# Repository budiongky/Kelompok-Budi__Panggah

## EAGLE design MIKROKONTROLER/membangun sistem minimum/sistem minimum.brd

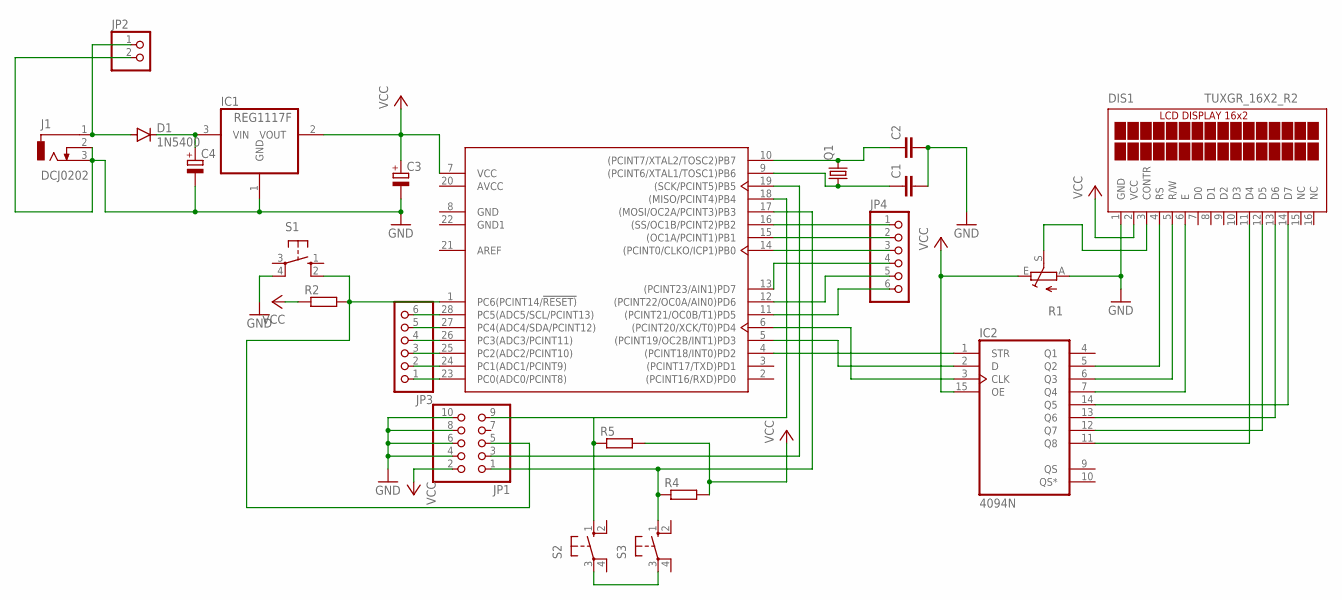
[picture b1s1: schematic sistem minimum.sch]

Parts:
C1, C2: C2,5-3; C2.5-3
C3, C4: CPOL-EUE2.5-6; E2,5-6
D1: 1N5400; DO201-15
DIS1: TUXGR_16X2_R2
IC1: REG1117F; DD-3
IC2: 4094N; DIL16
J1: DCJ0202
JP1: PINHD-2X5; 2X05
JP2: PINHD-1X2; 1X02
JP3, JP4: PINHD-1X6; 1X06
Q1: CRYSTALHC49S; HC49/S
R1: TRIM_EU-B25P; B25P
R2, R4, R5: R-EU_0204/7; 0204/7
S1, S2, S3: 10-XX; B3F-10XX
U1: ATMEGA328P-PU; DIP-28

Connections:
AVCC: U1.20 (AVCC)
GND: C1.2, C2.2, C3.-, C4.-, DIS1.1 (GND), IC1.1 (GND), J1.2, J1.3, JP1.4, JP1.6, JP1.8, JP1.10, JP2.2, R1.A, S1.4 (P1), U1.8 (GND)
GND1: U1.22 (GND1)
unnamed: C2.1, Q1.2, U1.10 ((PCINT7/XTAL2/TOSC2)PB7)
unnamed: C1.1, Q1.1, U1.9 ((PCINT6/XTAL1/TOSC1)PB6)
unnamed: JP1.9, U1.18 ((MISO/PCINT4)PB4)
unnamed: JP1.5, R2.2, S1.2 (S1), U1.1 (PC6(PCINT14/!RESET))
unnamed: JP1.3, U1.19 ((SCK/PCINT5)PB5)
unnamed: JP1.1, R4.1, S3.1 (S), U1.17 ((MOSI/OC2A/PCINT3)PB3)
unnamed: S2.3, S3.3
unnamed: C4.+, D1.C, IC1.3 (VIN)
unnamed: D1.A, J1.1, JP2.1
unnamed: R5.1, S2.1 (S)
unnamed: IC2.1 (STR), U1.4 ((PCINT18/INT0)PD2)
unnamed: IC2.2 (D), U1.5 ((PCINT19/OC2B/INT1)PD3)
unnamed: IC2.3 (CLK), U1.6 ((PCINT20/XCK/T0)PD4)
unnamed: DIS1.4 (RS), IC2.5 (Q2)
unnamed: DIS1.5 (R/W), IC2.6 (Q3)
unnamed: DIS1.6 (E), IC2.7 (Q4)
unnamed: DIS1.11 (D4), IC2.11 (Q8)
unnamed: DIS1.12 (D5), IC2.12 (Q7)
unnamed: DIS1.13 (D6), IC2.13 (Q6)
unnamed: DIS1.14 (D7), IC2.14 (Q5)
unnamed: JP3.6, U1.28 (PC5(ADC5/SCL/PCINT13))
unnamed: DIS1.3 (CONTR), R1.S
unnamed: JP3.5, U1.27 (PC4(ADC4/SDA/PCINT12))
unnamed: JP3.4, U1.26 (PC3(ADC3/PCINT11))
unnamed: JP3.3, U1.25 (PC2(ADC2/PCINT10))
unnamed: JP3.2, U1.24 (PC1(ADC1/PCINT9))
unnamed: JP3.1, U1.23 (PC0(ADC0/PCINT8))
unnamed: JP4.1, U1.16 ((SS/OC1B/PCINT2)PB2)
unnamed: JP4.2, U1.15 ((OC1A/PCINT1)PB1)
unnamed: JP4.3, U1.14 ((PCINT0/CLKO/ICP1)PB0)
unnamed: JP4.4, U1.13 ((PCINT23/AIN1)PD7)
unnamed: JP4.5, U1.12 ((PCINT22/OC0A/AIN0)PD6)
unnamed: JP4.6, U1.11 ((PCINT21/OC0B/T1)PD5)
VCC: C3.+, DIS1.2 (VCC), IC1.2 (VOUT), IC2.15 (OE), JP1.2, R1.E, R2.1, R4.2, R5.2, U1.7 (VCC)
VDD: IC2.16 (VDD)
VSS: IC2.8 (VSS)

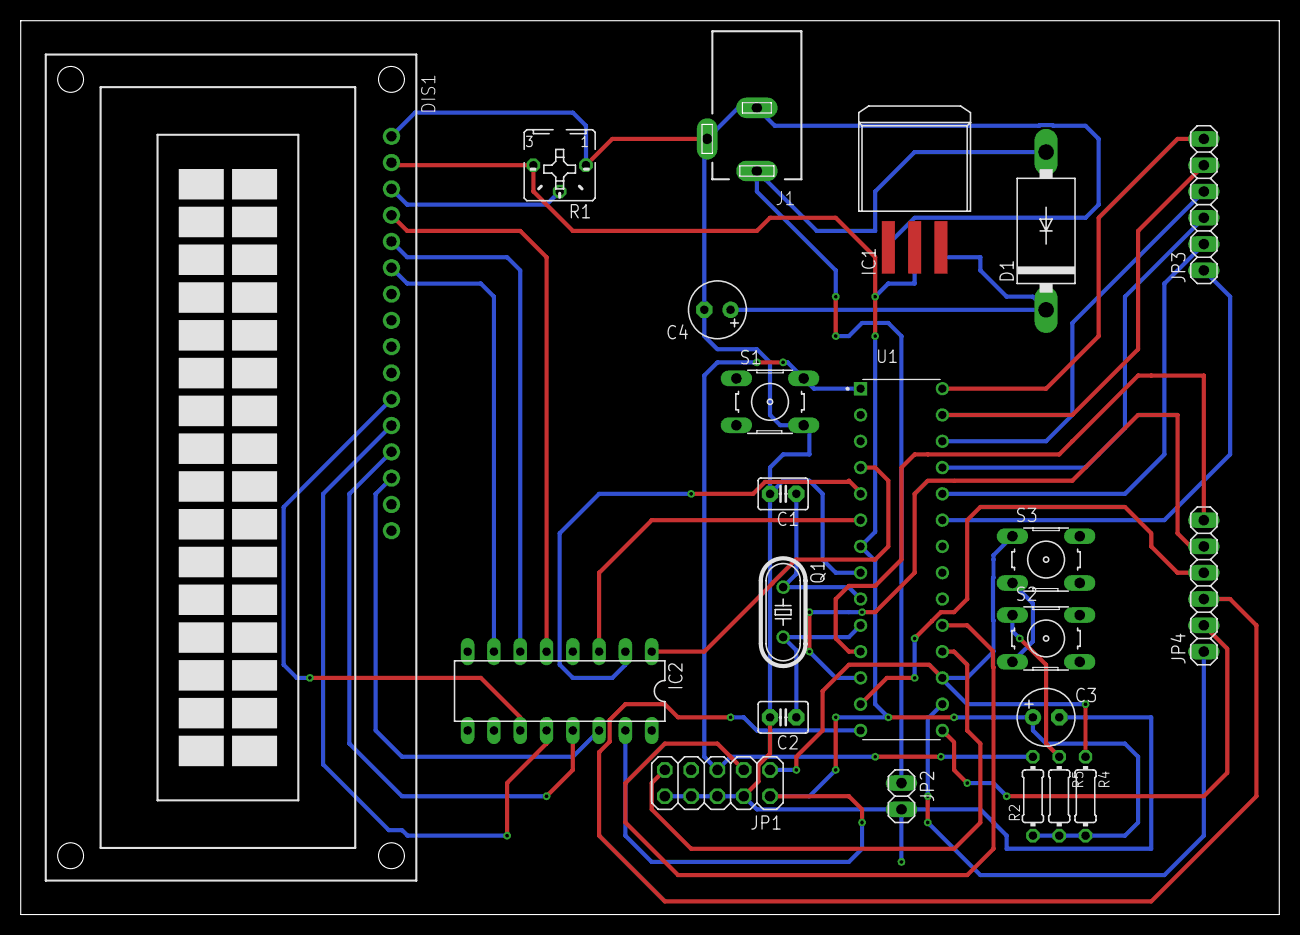
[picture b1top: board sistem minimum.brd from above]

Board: 2 copper layers, 121.6 x 86.3 mm, 22 parts (0 on the bottom side), 35 nets.

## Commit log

2021-03-08 perubahan di sistem kendali pwm
2021-03-09 Pengerjaan Sisken-sismin
2021-03-15 add sisken pwm last error
2021-04-14 praktikum mandiri
